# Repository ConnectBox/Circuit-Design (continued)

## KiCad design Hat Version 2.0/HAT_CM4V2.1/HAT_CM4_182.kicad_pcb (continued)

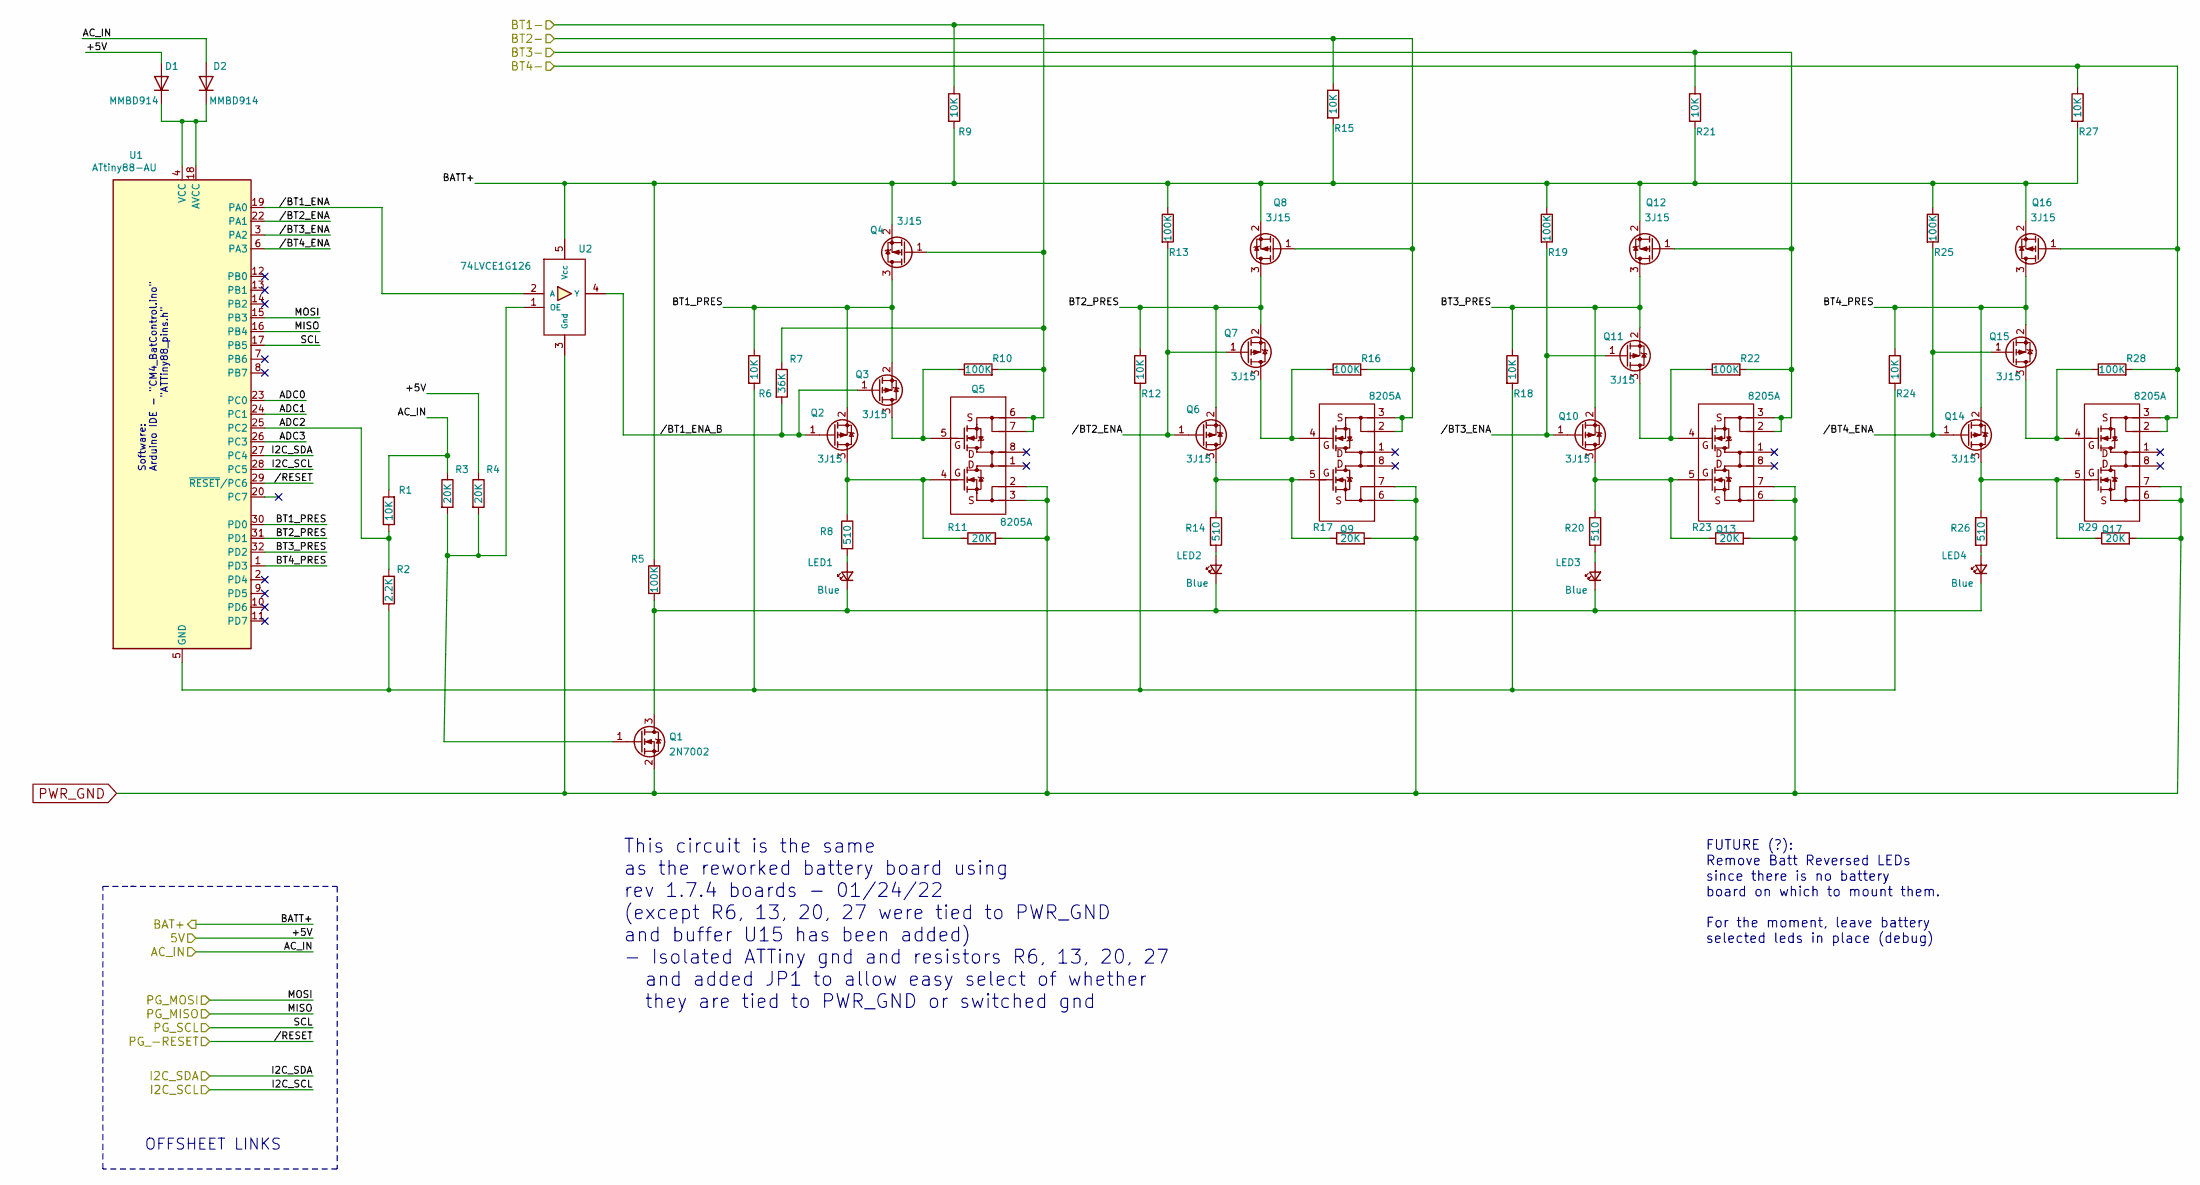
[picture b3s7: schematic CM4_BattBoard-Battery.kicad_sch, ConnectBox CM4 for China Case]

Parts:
D1, D2: MMBD914; D_SOT-23_ANK; Manufacturer P/N MMBD914LT1G; DigiKey P/N MMBD914LT1GOSCT-ND
LED1, LED2, LED3, LED4: Blue; LED_0603_1608Metric; Manufacturer P/N LTST-S270TBKT; DigiKey P/N 160-1650-1-ND
Q1: 2N7002; SOT-23; Manufacturer P/N T2N7002BK,LM; DigiKey P/N T2N7002BKLMCT-ND (alt: T2N7002AKLMCT-ND)
Q2, Q3, Q4, Q6, Q7, Q8, Q10, Q11, Q12, Q14, Q15, Q16: 3J15; SOT-323_SC-70; Manufacturer P/N SSM3J15FU,LF; DigiKey P/N SSM3J15FULFCT-ND
Q5, Q9, Q13, Q17: 8205A; TSSOP-8_4.4x3mm_P0.65mm; DigiKey P/N [none - from AliExpress|
R1: 10K; R_0603_1608Metric; Manufacturer P/N RC0603FR-0710KL; DigiKey P/N 311-10.0KHRCT-ND
R2: 2.2K; R_0603_1608Metric; Manufacturer P/N RC0603FR-072K2L; DigiKey P/N 311-2.20KHRCT-ND
R3, R4, R11, R17, R23, R29: 20K; R_0603_1608Metric; Manufacturer P/N RC0603FR-0720KL; DigiKey P/N 311-20.0KHRCT-ND
R5, R10, R13, R16, R19, R22, R25, R28: 100K; R_0603_1608Metric; Manufacturer P/N RC0603FR-07100KL; DigiKey P/N 311-100KHRCT-ND
R6, R9, R12, R15, R18, R21, R24, R27: 10K; R_0603_1608Metric; Manufacturer P/N RC0603FR-0710KL; DigiKey P/N 311-10KHRCT-ND
R7: 36K; R_0603_1608Metric; Manufacturer P/N RC0603FR-0736KL; DigiKey P/N 311-36.0KHRCT-ND
R8, R14, R20, R26: 510; R_0603_1608Metric; Manufacturer P/N RC0603FR-07510RL; DigiKey P/N 311-510HRCT-ND
U1: ATtiny88-AU; TQFP-32_7x7mm_P0.8mm; Manufacturer P/N ATTINY88-AU; DigiKey P/N ATTINY88-AU-ND
U2: 74LVCE1G126; SOT-23-5; Manufacturer P/N 74LVCE1G126W5-7; DigiKey P/N 74LVCE1G126W5-7DICT-ND

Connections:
+5V: D1.2 (A), R4.1; also elsewhere on the board
/AC_IN: D2.2 (A), R1.2, R3.1; also elsewhere on the board
/Batteries/BT1-: Q4.1 (G), Q5.6 (S2), Q5.7 (S2), R7.1, R9.1, R10.2; also elsewhere on the board
/Batteries/BT2-: Q8.1 (G), Q9.2 (S1), Q9.3 (S1), R15.1, R16.2; also elsewhere on the board
/Batteries/BT3-: Q12.1 (G), Q13.2 (S1), Q13.3 (S1), R21.1, R22.2; also elsewhere on the board
/Batteries/BT4-: Q16.1 (G), Q17.2 (S1), Q17.3 (S1), R27.1, R28.2; also elsewhere on the board
/Battery/ADC0: U1.23 (PC0)
/Battery/ADC1: U1.24 (PC1)
/Battery/ADC2: R1.1, R2.1, U1.25 (PC2)
/Battery/ADC3: U1.26 (PC3)
/Battery/BATT+: Q4.2 (S), Q8.2 (S), Q12.2 (S), Q16.2 (S), R5.1, R9.2, R13.1, R15.2, R19.1, R21.2, R25.1, R27.2, U2.5 (Vcc); also elsewhere on the board
/Battery/BT1_PRES: Q2.2 (S), Q3.2 (S), Q4.3 (D), R6.1, U1.30 (PD0)
/Battery/BT2_PRES: Q6.2 (S), Q7.2 (S), Q8.3 (D), R12.1, U1.31 (PD1)
/Battery/BT3_PRES: Q10.2 (S), Q11.2 (S), Q12.3 (D), R18.1, U1.32 (PD2)
/Battery/BT4_PRES: Q14.2 (S), Q15.2 (S), Q16.3 (D), R24.1, U1.1 (PD3)
/Battery/I2C_SCL: U1.28 (PC5); also elsewhere on the board
/Battery/I2C_SDA: U1.27 (PC4); also elsewhere on the board
/Battery/MISO: U1.16 (PB4); also elsewhere on the board
/Battery/MOSI: U1.15 (PB3); also elsewhere on the board
/Battery/SCL: U1.17 (PB5); also elsewhere on the board
/Battery//BT1_ENA: U1.19 (PA0), U2.2 (A)
/Battery//BT1_ENA_B: Q2.1 (G), Q3.1 (G), R7.2, U2.4 (Y)
/Battery//BT2_ENA: Q6.1 (G), Q7.1 (G), R13.2, U1.22 (PA1)
/Battery//BT3_ENA: Q10.1 (G), Q11.1 (G), R19.2, U1.3 (PA2)
/Battery//BT4_ENA: Q14.1 (G), Q15.1 (G), R25.2, U1.6 (PA3)
/Battery//RESET: U1.29 (~RESET/PC6); also elsewhere on the board
unnamed: D1.1 (K), D2.1 (K), U1.4 (VCC), U1.18 (AVCC)
unnamed: LED1.1 (K), LED2.1 (K), LED3.1 (K), LED4.1 (K), Q1.3 (D), R5.2
unnamed: LED1.2 (A), R8.2
unnamed: LED2.2 (A), R14.2
unnamed: LED3.2 (A), R20.2
unnamed: LED4.2 (A), R26.2
unnamed: Q1.1 (G), R3.2, R4.2, U2.1 (OE)
unnamed: Q2.3 (D), Q5.4 (G1), R8.1, R11.1
unnamed: Q3.3 (D), Q5.5 (G2), R10.1
unnamed: Q6.3 (D), Q9.5 (G2), R14.1, R17.1
unnamed: Q7.3 (D), Q9.4 (G1), R16.1
unnamed: Q10.3 (D), Q13.5 (G2), R20.1, R23.1
unnamed: Q11.3 (D), Q13.4 (G1), R22.1
unnamed: Q14.3 (D), Q17.5 (G2), R26.1, R29.1
unnamed: Q15.3 (D), Q17.4 (G1), R28.1
unnamed: R2.2, R6.2, R12.2, R18.2, R24.2, U1.5 (GND), U1.21 (GND)
PWR_GND: Q1.2 (S), Q5.2 (S1), Q5.3 (S1), Q9.6 (S2), Q9.7 (S2), Q13.6 (S2), Q13.7 (S2), Q17.6 (S2), Q17.7 (S2), R11.2, R17.2, R23.2, R29.2, U2.3 (Gnd); also elsewhere on the board

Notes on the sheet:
This circuit is the same as the reworked battery board using rev 1.7.4 boards - 01/24/22 (except R6, 13, 20, 27 were tied to PWR_GND and buffer U15 has been added) - Isolated ATTiny gnd and resistors R6, 13, 20, 27 and added JP1 to allow easy select of whether they are tied to PWR_GND or switched g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
FUTURE (?): Remove Batt Reversed LEDs since there is no battery board on which to mount them. For the moment, leave battery selected leds in place (debug)
Software: Arduino IDE - "CM4_BatControl.ino" "ATTiny88_pins.h"
OFFSHEET LINKS

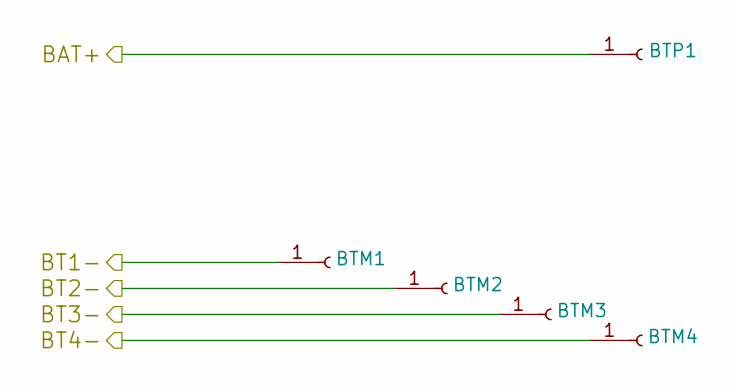
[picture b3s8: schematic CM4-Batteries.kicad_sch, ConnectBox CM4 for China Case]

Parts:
BTM1, BTM2, BTM3, BTM4: Conn_01x01_Female; WH-Battery-
BTP1: Conn_01x01_Female; TestPoint_THTPad_2.0x2.0mm_Drill1.0mm

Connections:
/Batteries/BT1-: BTM1.1; also elsewhere on the board
/Batteries/BT2-: BTM2.1; also elsewhere on the board
/Batteries/BT3-: BTM3.1; also elsewhere on the board
/Batteries/BT4-: BTM4.1; also elsewhere on the board
/Battery/BATT+: BTP1.1; also elsewhere on the board

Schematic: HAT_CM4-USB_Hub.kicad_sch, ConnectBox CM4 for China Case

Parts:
C23, C24: 9pF; C_0603_1608Metric; Manufacturer P/N CGA3E2C0G1H090D080AA; DigiKey P/N 445-5627-1-ND
C25, C26, C27, C32, C34, C36, C38: 10uF; C_0603_1608Metric; Manufacturer P/N C0603C106M9PACTU; DigiKey P/N 399-C0603C106M9PAC7867CT-ND
C28, C29, C31, C33, C35, C37: 0.1uf; C_0603_1608Metric; Manufacturer P/N C0603C104K9PAC7867; DigiKey P/N 399-17575-1-ND
C30: 100uF; CP_Elec_6.3x4.5; Manufacturer P/N RSL0J101MCN1GB; DigiKey P/N 493-3819-1-ND
C39, C40: 22uF; C_0603_1608Metric; Manufacturer P/N CL10A226MQ8NRNC; DigiKey P/N 1276-1193-1-ND
J3, J4: USB_A; USB_A_CUI_smd; Manufacturer P/N UJ2-AH-1-SMT-TR; DigiKey P/N 102-4133-1-ND
J5: USB-C; USB-C-GCT; Manufacturer P/N USB4105-GF-A; DigiKey P/N 2073-USB4105-GF-ACT-ND
R51, R52, R53, R55: 36K; R_0603_1608Metric; Manufacturer P/N RC0603FR-0736KL; DigiKey P/N 311-36.0KHRCT-ND
R54: 12K; R_0603_1608Metric; Manufacturer P/N RC0603FR-0712KL; DigiKey P/N 311-12.0KHRCT-ND
U12: RT9742ANGJ5F; SOT-23-5; Manufacturer P/N RT9742ANGJ5F; DigiKey P/N 1028-1427-1-ND
U13: USB2514B-I/M2; QFN-36-1EP_6x6mm_P0.5mm_EP3.7x3.7mm; Manufacturer P/N USB2514B-I/M2; DigiKey P/N USB2514B/M2-ND
U15: HC-R8812AF1; HC-R8812AU2; DigiKey P/N [none - see Kirk for order details]
Y1: 24MHz; Crystal_SMD_HC49-SD; Manufacturer P/N QCS24.0000F18B23M; DigiKey P/N Newark: 2508493

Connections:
+3.3v: C26.1, C27.1, C28.1, C29.1, C31.1, C33.1, C35.1, C37.1, C40.1, U13.5 (VDDA33), U13.10 (VDDA33), U13.15 (VDD33), U13.23 (VDD33), U13.27 (VBUS_DET), U13.29 (VDDA33), U13.36 (VDDA33), U15.1 (PDN), U15.2 (3.3V); also elsewhere on the board
+5V: C25.1, U12.5 (VIN); also elsewhere on the board
/AC_IN: C39.1, J5.A4/B9 (Power), J5.B4/A9 (Power); also elsewhere on the board
/CM4_HighSpeed/USB2_N: U13.31 (USBDP_UP); also elsewhere on the board
/CM4_HighSpeed/USB2_P: U13.30 (USBDM_UP); also elsewhere on the board
/USB Hub/HD1_N: U13.1 (USBDM_DN1/PRT_DIS_M1)
/USB Hub/HD1_P: U13.2 (USBDP_DN1/PRT_DIS_P1)
/USB Hub/HD2_N: U13.3 (USBDM_DN2/PRT_DIS_M2), U15.3 (DM-)
/USB Hub/HD2_P: U13.4 (USBDP_DN2/PRT_DIS_P2), U15.4 (DP+)
/USB Hub/HD3_N: J4.2 (D-), U13.6 (USBDM_DN3/PRT_DIS_M3)
/USB Hub/HD3_P: J4.3 (D+), U13.7 (USBDP_DN3/PRT_DIS_P3)
/USB Hub/HD4_N: J3.2 (D-), U13.8 (USBDM_DN4/PRT_DIS_M4)
/USB Hub/HD4_P: J3.3 (D+), U13.9 (USBDP_DN4/PRT_DIS_P4)
/USB Hub/PWR1: U12.4 (EN), U13.12 (PRTPWR1/BC_EN1)
/USB Hub/VBUS: C30.1, C32.1, C34.1, C36.1, C38.1, J3.1 (VBUS), J4.1 (VBUS), U12.1 (VOUT)
/USB Hub/nEXTRST: U13.26 (RESET_N); also elsewhere on the board
/USB Hub/nOCS1: U12.3 (/FLG), U13.13 (OCS_N1), U13.17 (OCS_N2), U13.19 (OCS_N3), U13.21 (OCS_N4)
GND: C23.2, C24.2, C25.2, C26.2, C27.2, C28.2, C29.2, C30.2, C31.2, C32.2, C33.2, C34.2, C35.2, C36.2, C37.2, C38.2, C39.2, C40.2, J3.4 (GND), J3.5 (Shield), J4.4 (GND), J4.5 (Shield), J5.1 (Shell), J5.A1/B12 (GND), J5.B1/A12 (GND), R51.2, R52.2, R53.2, R54.1, R55.2, U12.2 (GND), U13.37 (VSS), U15.5 (GND), U15.7 (GND), U15.9 (GND), U15.10 (GND), U15.12 (GND), U15.13 (GND), U15.14 (GND), U15.15 (GND); also elsewhere on the board
unnamed: C23.1, U13.33 (XTALIN/CLKIN), Y1.1
unnamed: C24.1, U13.32 (XTALOUT), Y1.2
unnamed: R51.1, U13.24 (SCL/SMBCLK/CFG_SEL0)
unnamed: R52.1, U13.22 (SDA/SMBDATA/NON_REM1)
unnamed: R53.1, U13.28 (SUSP_IND/LOCAL_PWR/NON_REM0)
unnamed: R54.2, U13.35 (RBIAS)
unnamed: R55.1, U13.25 (HS_IND/CFG_SEL1)

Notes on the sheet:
Current Limit switch
USB-C cannot be used both for charging input and data source (AC_IN cannot be tied to 5V or AXP209 causes 5V to toggle on and off)
USB 2.0 Hub
OTG
VBUS is a 5v current protected source
WiFi Module

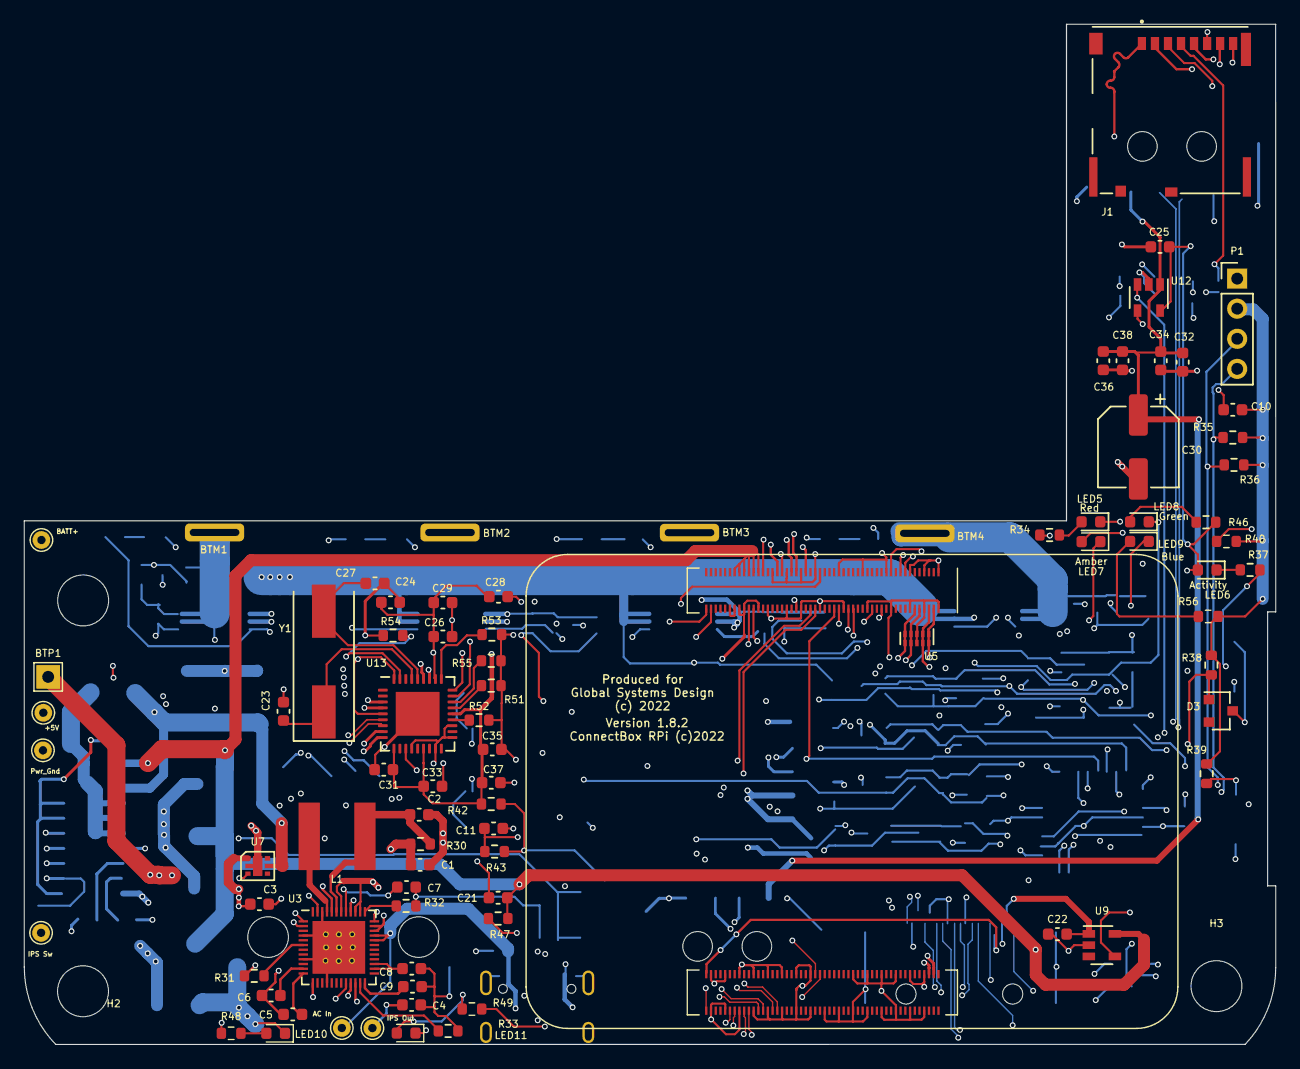
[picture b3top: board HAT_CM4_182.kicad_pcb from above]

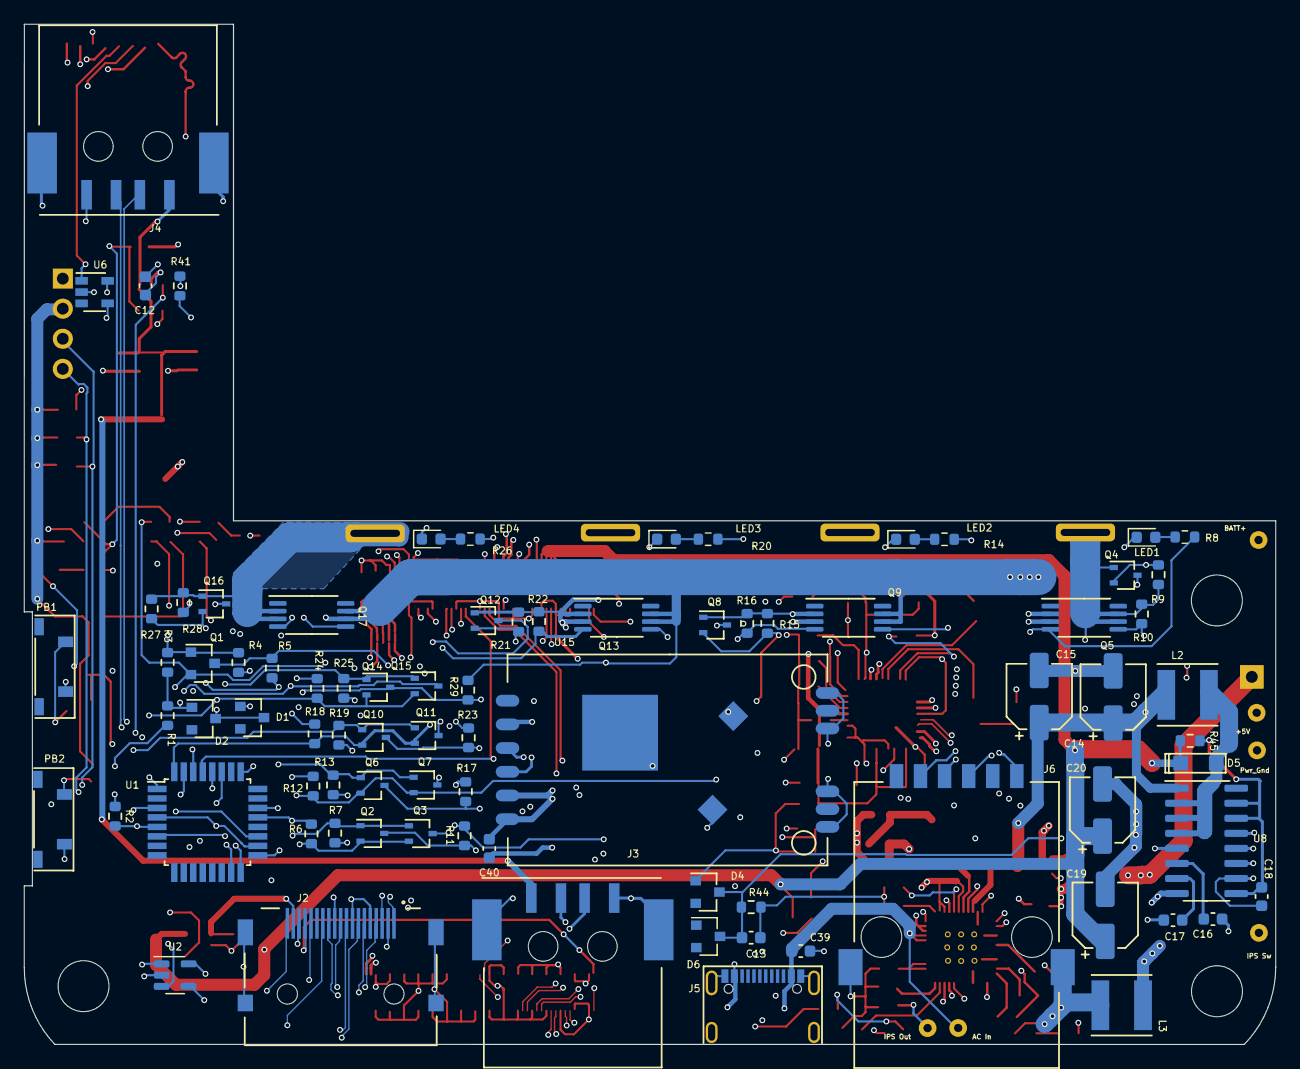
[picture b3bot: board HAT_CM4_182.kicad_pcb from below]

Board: 6 copper layers, 105.6 x 86.1 mm, 168 parts (83 on the bottom side), 123 nets.
